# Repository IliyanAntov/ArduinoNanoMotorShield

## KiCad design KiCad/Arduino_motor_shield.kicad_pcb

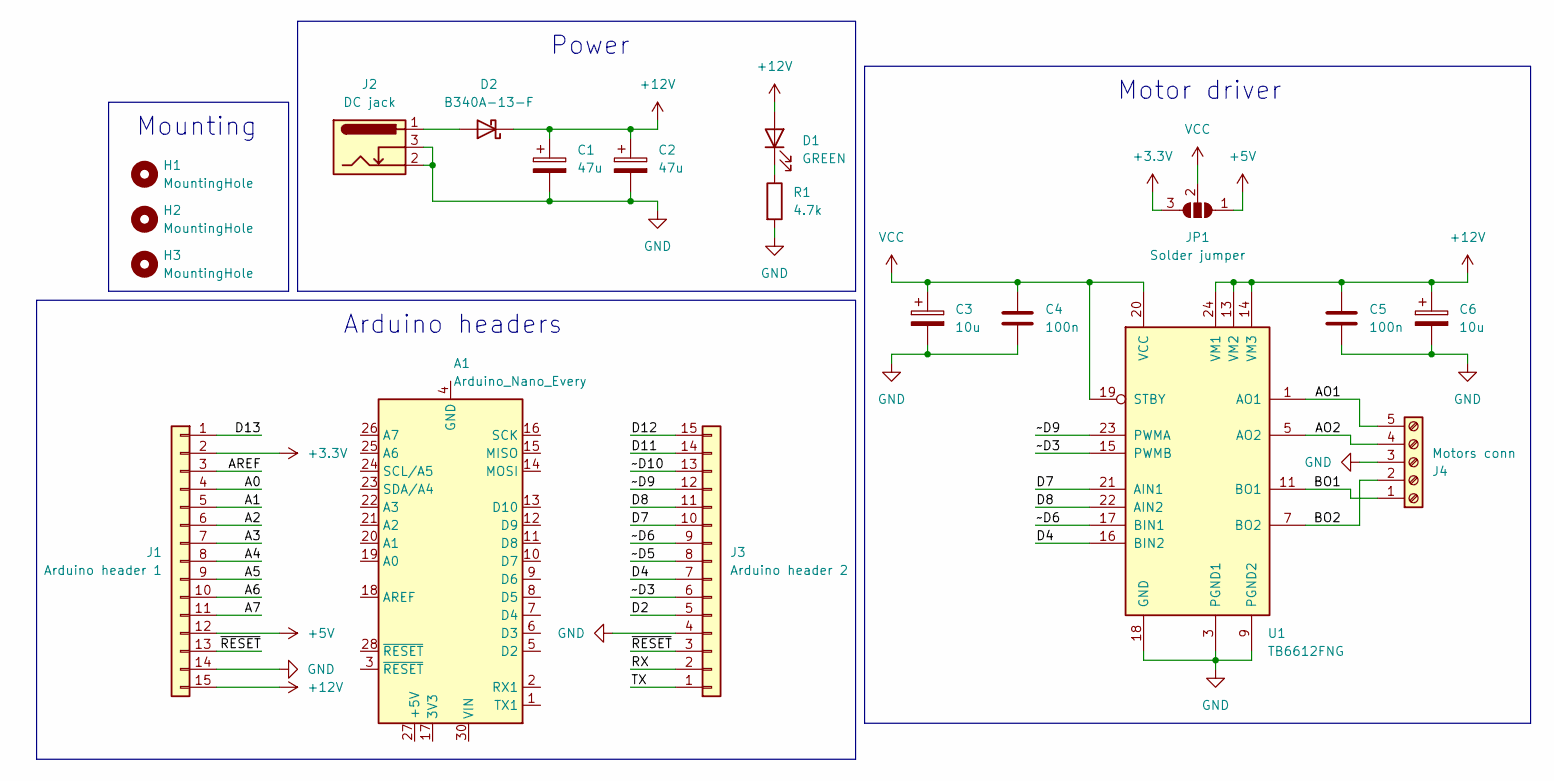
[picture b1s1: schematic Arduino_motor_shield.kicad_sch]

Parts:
A1: Arduino_Nano_Every; Arduino_Nano
C1, C2: 47u; CP_Elec_6.3x5.8
C3, C6: 10u; CP_Elec_5x5.4
C4, C5: 100n; C_0805_2012Metric_Pad1.18x1.45mm_HandSolder
D1: GREEN; LED_0805_2012Metric_Pad1.15x1.40mm_HandSolder
D2: B340A-13-F; D_SMA_Handsoldering
H1, H2, H3: MountingHole; MountingHole_2.2mm_M2_ISO7380
J1: Arduino header 1; PinSocket_1x15_P2.54mm_Vertical
J2: DC jack; BarrelJack_Horizontal
J3: Arduino header 2; PinSocket_1x15_P2.54mm_Vertical
J4: Motors conn; TerminalBlock_Phoenix_MKDS-1,5-5_1x05_P5.00mm_Horizontal
JP1: Solder jumper; SolderJumper-3_P1.3mm_Open_Pad1.0x1.5mm
R1: 4.7k; R_0805_2012Metric_Pad1.20x1.40mm_HandSolder
U1: TB6612FNG; SSOP-24_5.3x8.2mm_P0.65mm

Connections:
+3.3V: J1.2, JP1.3 (B)
+5V: J1.12, JP1.1 (A)
+12V: C1.1, C2.1, C5.1, C6.1, D1.2 (A), D2.1 (K), J1.15, U1.13 (VM2), U1.14 (VM3), U1.24 (VM1)
/A0: J1.4
/A1: J1.5
/A2: J1.6
/A3: J1.7
/A4: J1.8
/A5: J1.9
/A6: J1.10
/A7: J1.11
/AO1: J4.5, U1.1 (AO1), U1.2 (AO1)
/AO2: J4.4, U1.5 (AO2), U1.6 (AO2)
/AREF: J1.3
/BO1: J4.1, U1.11 (BO1), U1.12 (BO1)
/BO2: J4.2, U1.7 (BO2), U1.8 (BO2)
/D2: J3.5
/D4: J3.7, U1.16 (BIN2)
/D7: J3.10, U1.21 (AIN1)
/D8: J3.11, U1.22 (AIN2)
/D11: J3.14
/D12: J3.15
/D13: J1.1
/RX: J3.2
/TX: J3.1
/~D3: J3.6, U1.15 (PWMB)
/~D5: J3.8
/~D6: J3.9, U1.17 (BIN1)
/~D9: J3.12, U1.23 (PWMA)
/~D10: J3.13
/~RESET: J1.13, J3.3
GND: C1.2, C2.2, C3.2, C4.2, C5.2, C6.2, J1.14, J2.2, J2.3, J3.4, J4.3, R1.2, U1.3 (PGND1), U1.4 (PGND1), U1.9 (PGND2), U1.10 (PGND2), U1.18 (GND)
unnamed: A1.4 (GND), A1.29 (GND)
unnamed: D1.1 (K), R1.1
unnamed: D2.2 (A), J2.1
VCC: C3.1, C4.1, JP1.2 (C), U1.19 (STBY), U1.20 (VCC)

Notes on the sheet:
Power
Arduino headers
Mounting
Motor driver

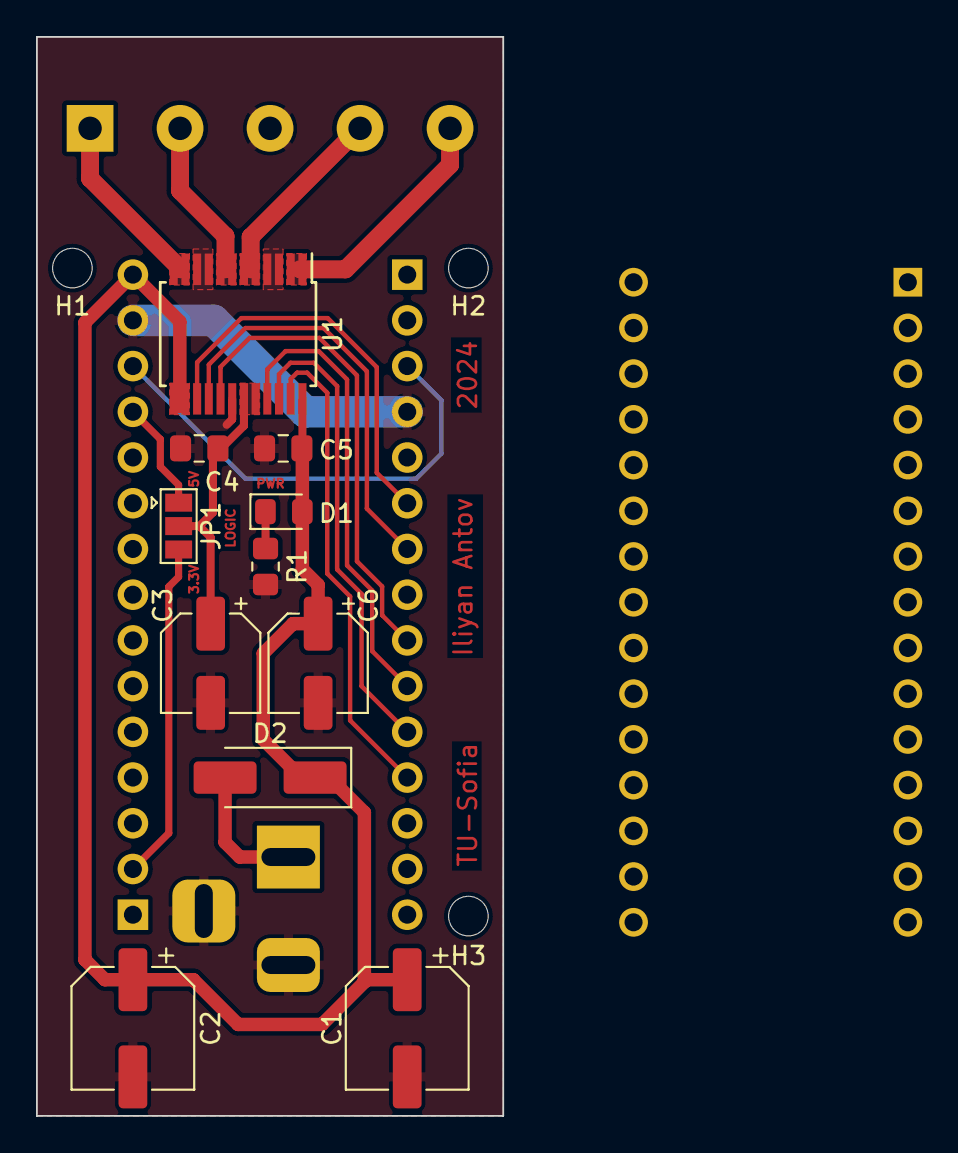
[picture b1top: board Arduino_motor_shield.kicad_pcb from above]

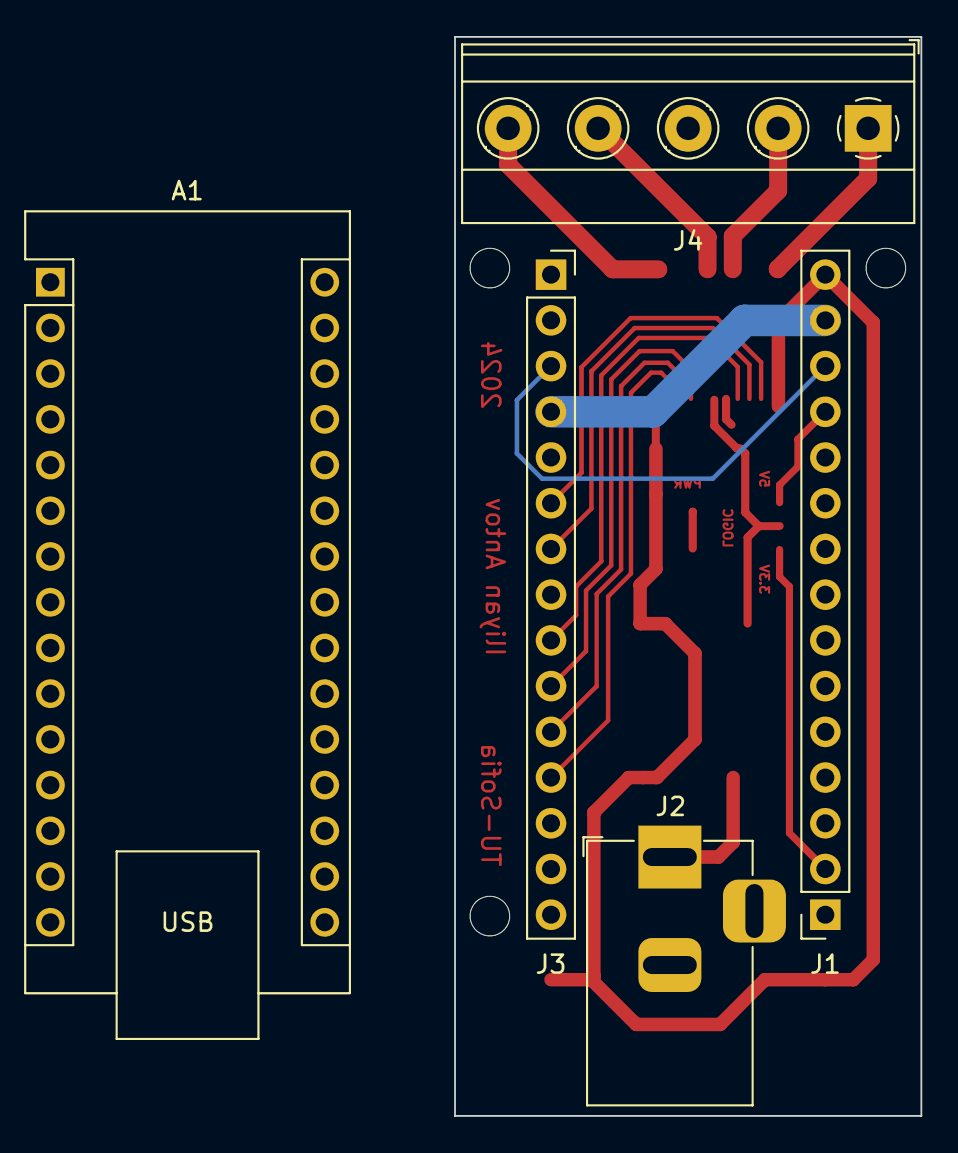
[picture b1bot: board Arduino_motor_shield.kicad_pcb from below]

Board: 2 copper layers, 25.9 x 59.9 mm, 19 parts (5 on the bottom side), 19 nets.

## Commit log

2024-02-27 Created initial version of schematic and PCB
2024-02-27 Small fixes to alignment
2024-02-28 Added mounting holes
2024-02-29 Freed up a PWM pin on the Arduino
2024-03-01 Added manufacture data PDF
